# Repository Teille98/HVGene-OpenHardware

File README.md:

# HVGene — Open-Source High-Voltage Power Supply for Cold Atmospheric Plasma

Open-source, digitally controlled high-voltage AC power supply for cold atmospheric
plasma (CAP) research, developed with a specific focus on flexible-endoscope
decontamination applications. The platform delivers either continuous sinusoidal
high-voltage excitation or pulsed AC trains, with explicit user control over input
voltage, operating frequency, duty cycle, timing, and operating mode.

This repository accompanies the following HardwareX article:

> *Open-Source High Voltage Power Supply for Cold Atmospheric Plasma Generation*,
> HardwareX (2026). DOI: _to be added once assigned_.

Archived on Zenodo: [10.5281/zenodo.21889908](https://doi.org/10.5281/zenodo.21889908).

If you use this hardware, firmware, or documentation, please cite the article above.

## Repository structure

This project mixes three kinds of content, each released under the license most
appropriate for that kind of content — see the `LICENSE` file inside each folder
for the exact terms.

```
HVGene_OpenHardware/
├── hardware/          Electronics and mechanical design files
│   ├── LICENSE        CERN-OHL-P-2.0 (permissive open hardware licence, unmodified)
│   ├── NOTICE          Copyright notice (kept separate — the licence text itself
│   │                   must not be modified, per its own Preamble)
│   ├── KiCAD/          PCB schematic and layout (push-pull inverter board);
│   │                   Article_Figure3_version/ = schematic as drawn in Figure 3
│   │                   of the article
│   ├── CAD-Fusion360/  3D mechanical design (enclosure, mounting)
│   ├── Cutting/        Laser-cutting SVG files (LV/HV plates)
│   └── BOM.xlsx        Bill of materials
├── firmware/           RP2040 / MicroPython control firmware
│   ├── LICENSE          MIT
│   ├── main.py, lib/    Firmware source
│   └── tests/           Bench validation scripts (I2C, PIO, timing)
├── docs/                Build photos, diagrams, and other documentation media
│   ├── LICENSE           CC BY-SA 4.0
│   └── Figures/          Article_Figures/ = the article figures (Fig01–Fig29) and
│                         Supplementary Material figures (FigS1–FigS6); plus
│                         device/setup/plasma photos, CAD renders, diagrams (with
│                         their draw.io/TikZ sources), build-step and scope images
└── data/                Validation dataset (all measured operating points, raw and
                          derived quantities) behind the article's validation section
```

The folders above are the design files listed in the article's *Design files
summary* (Table 3).

## Versioning

The version tagged and archived alongside the HardwareX article submission is the
exact hardware/firmware state described and validated in that article. This
repository may continue to evolve after that point (bug fixes, improvements,
community contributions); the archived release is the one to use for reproducing
the results reported in the article.

## Safety

This hardware generates high voltages (up to several tens of kV) and involves
mains-connected power electronics. Building and operating it requires
appropriate electrical safety training. See the "Safety Concerns" and
"Operation instructions" sections of the article before use.

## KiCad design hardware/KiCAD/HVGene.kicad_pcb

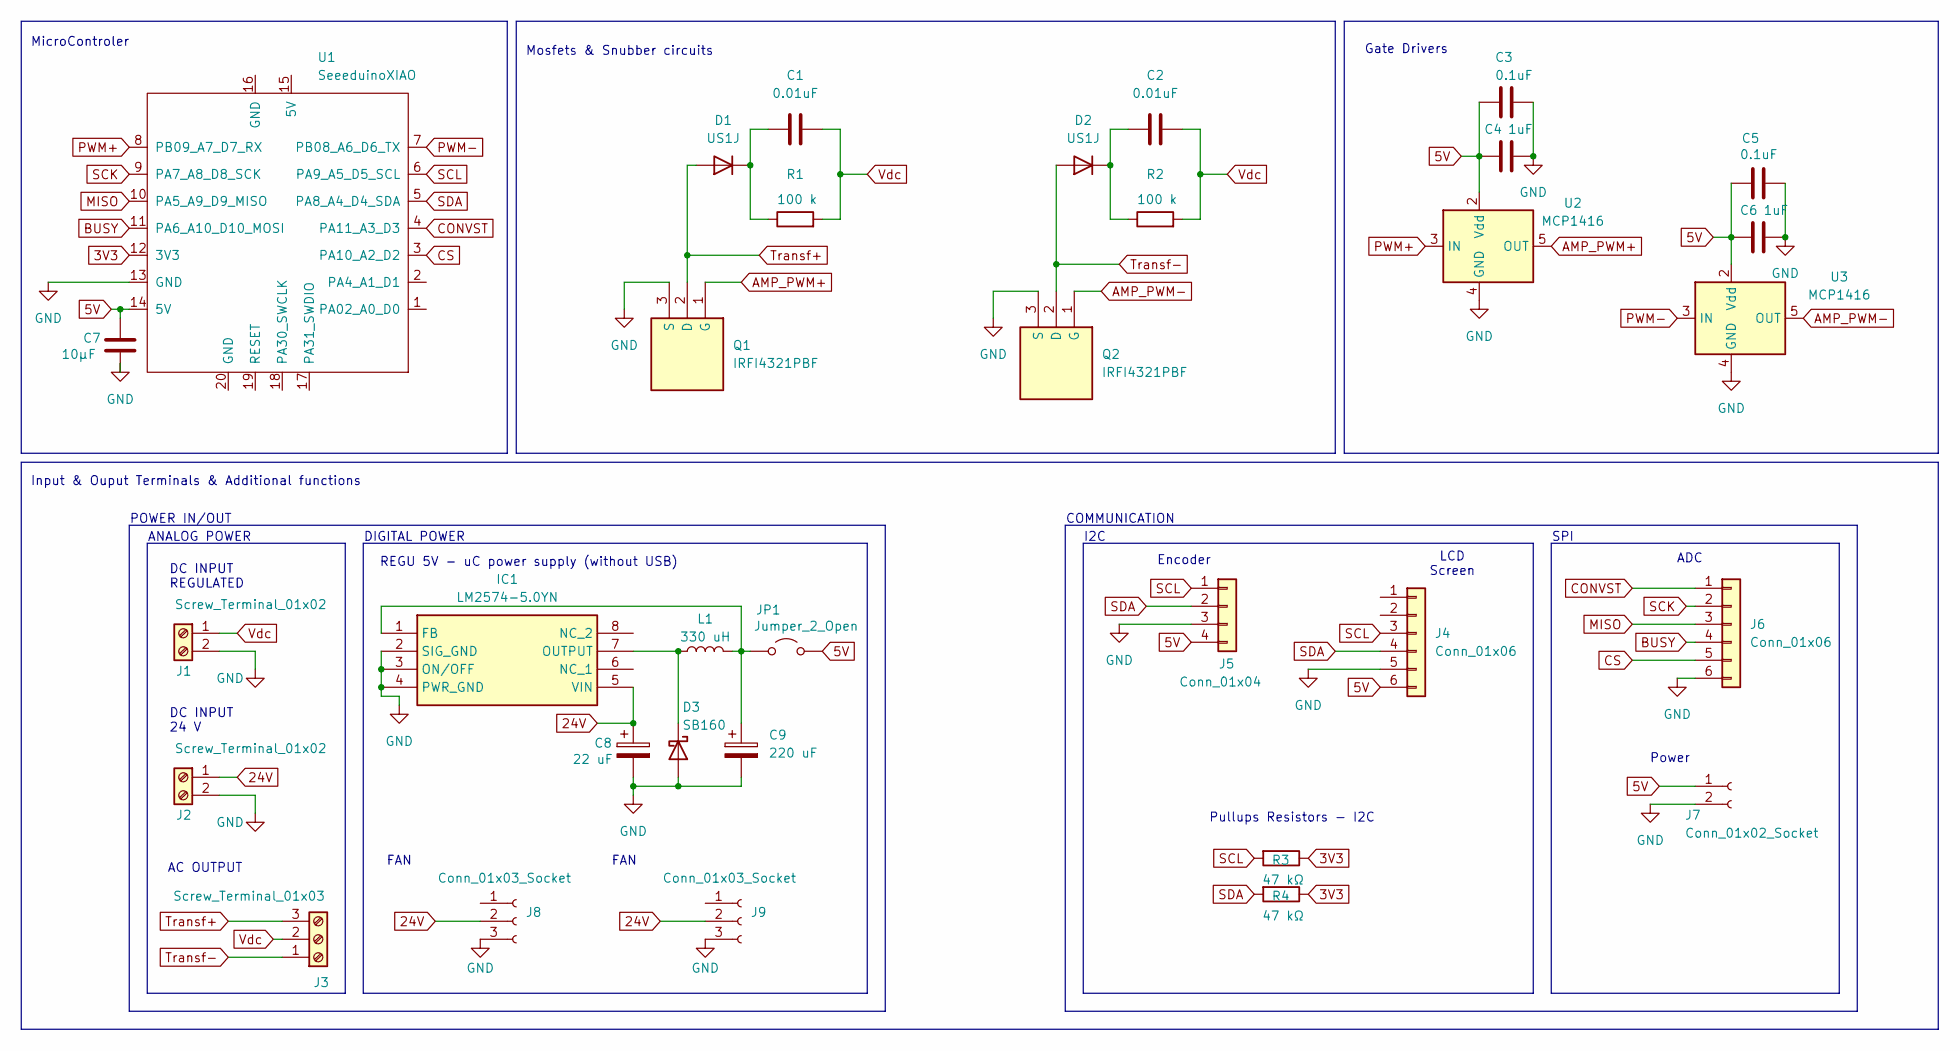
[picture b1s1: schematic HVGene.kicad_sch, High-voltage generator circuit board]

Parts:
C1, C2: 0.01uF; C_Rect_L7.0mm_W3.5mm_P5.00mm
C3, C5: 0.1uF; C_Rect_L7.0mm_W3.5mm_P5.00mm
C4, C6: 1uF; C_Rect_L7.0mm_W4.5mm_P5.00mm
C7: 10µF; C_Rect_L7.0mm_W4.5mm_P5.00mm
C8: 22 uF; CAPPRD200W52D500H1250
C9: 220 uF; CAPPRD500W60D1000H1350
D1, D2: US1J; D_DO-41_SOD81_P2.54mm_Vertical_AnodeUp
D3: SB160; DIOAD1405W86L465D235
IC1: LM2574-5.0YN; DIP762W57P254L952H343Q8N; Mouser Part Number 998-LM2574-5.0YN
J1, J2: Screw_Terminal_01x02; PhoenixContact_MSTBA_2,5_2-G-5,08_1x02_P5.08mm_Horizontal
J3: Screw_Terminal_01x03; PhoenixContact_MSTBA_2,5_3-G-5,08_1x03_P5.08mm_Horizontal
J4, J6: Conn_01x06; JST_XH_B6B-XH-A_1x06_P2.50mm_Vertical
J5: Conn_01x04; JST_XH_B4B-XH-A_1x04_P2.50mm_Vertical
J7: Conn_01x02_Socket; JST_XH_B2B-XH-A_1x02_P2.50mm_Vertical
J8, J9: Conn_01x03_Socket; JST_XH_B3B-XH-A_1x03_P2.50mm_Vertical
JP1: Jumper_2_Open; PinHeader_1x02_P2.54mm_Vertical
L1: 330 uH; WE-TIS_111190
Q1, Q2: IRFI4321PBF; TO254P483X1018X2095-3P; Mouser Part Number 942-IRFI4321PBF
R1, R2: 100 k; R_Axial_DIN0516_L15.5mm_D5.0mm_P5.08mm_Vertical
R3, R4: 47 kΩ; R_Axial_DIN0207_L6.3mm_D2.5mm_P2.54mm_Vertical
U1: SeeeduinoXIAO; SeeedStudio_XIAO_RP2040
U2, U3: MCP1416; SOT-23-5

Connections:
3V3: R3.1, R4.1, U1.12 (3V3); also elsewhere on the board
5V: C3.1, C4.1, C5.1, C6.1, C7.1, J4.6, J5.4, J7.1, JP1.2 (B), U1.14 (5V), U2.2 (Vdd), U3.2 (Vdd)
24V: C8.1, IC1.5 (VIN), J2.1, J8.2, J9.2
AMP_PWM+: Q1.1 (G), U2.5 (OUT)
AMP_PWM-: Q2.1 (G), U3.5 (OUT)
BUSY: J6.4, U1.11 (PA6_A10_D10_MOSI)
CONVST: J6.1, U1.4 (PA11_A3_D3)
CS: J6.5, U1.3 (PA10_A2_D2)
GND: C3.2, C4.2, C5.2, C6.2, C7.2, C8.2, C9.2, D3.2 (A), IC1.2 (SIG_GND), IC1.3 (ON/OFF), IC1.4 (PWR_GND), J1.2, J2.2, J4.5, J5.3, J6.6, J7.2, J8.3, J9.3, Q1.3 (S), Q2.3 (S), U1.13 (GND), U2.4 (GND), U3.4 (GND)
MISO: J6.3, U1.10 (PA5_A9_D9_MISO)
unnamed: C1.2, D1.1 (K), R1.1
unnamed: C2.2, D2.1 (K), R2.1
unnamed: D3.1 (K), IC1.7 (OUTPUT), L1.1
unnamed: C9.1, IC1.1 (FB), JP1.1 (A), L1.2
PWM+: U1.8 (PB09_A7_D7_RX), U2.3 (IN)
PWM-: U1.7 (PB08_A6_D6_TX), U3.3 (IN)
SCK: J6.2, U1.9 (PA7_A8_D8_SCK)
SCL: J4.3, J5.1, R3.2, U1.6 (PA9_A5_D5_SCL); also elsewhere on the board
SDA: J4.4, J5.2, R4.2, U1.5 (PA8_A4_D4_SDA)
Transf+: D1.2 (A), J3.3, Q1.2 (D)
Transf-: D2.2 (A), J3.1, Q2.2 (D)
Vdc: C1.1, C2.1, J1.1, J3.2, R1.2, R2.2

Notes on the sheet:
Pullups Resistors - I2C
DC INPUT REGULATED
FAN
REGU 5V - uC power supply (without USB)
Power
DC INPUT 24 V
POWER IN/OUT
ANALOG POWER
I2C
COMMUNICATION
MicroControler
SPI
Input & Ouput Terminals & Additional functions
Mosfets & Snubber circuits
AC OUTPUT
Gate Drivers
DIGITAL POWER
Encoder
LCD Screen
ADC

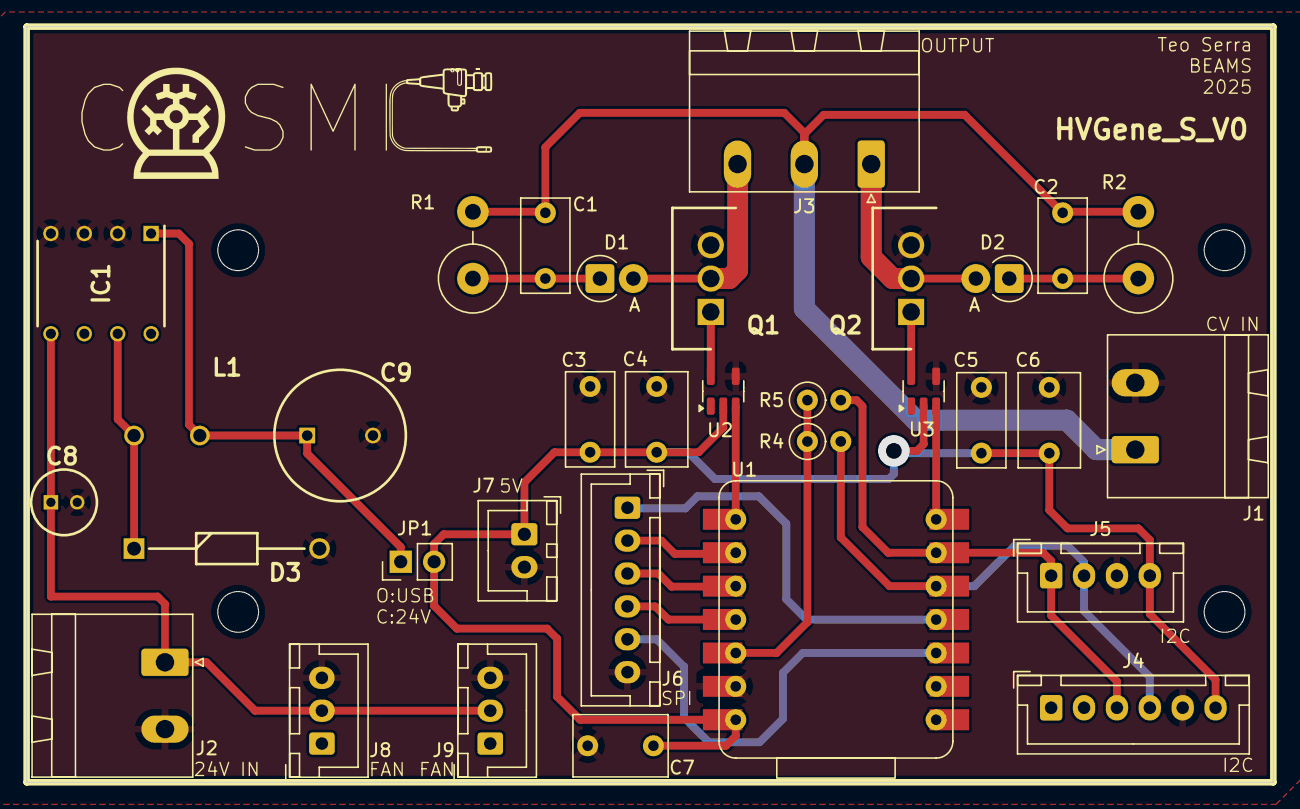
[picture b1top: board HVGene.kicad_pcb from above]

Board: 2 copper layers, 94.8 x 57.5 mm, 33 parts (0 on the bottom side), 22 nets.

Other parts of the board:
R5: 47 kΩ; R_Axial_DIN0207_L6.3mm_D2.5mm_P2.54mm_Vertical

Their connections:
3V3: R5.1; also elsewhere on the board
SCL: R5.2; also elsewhere on the board
